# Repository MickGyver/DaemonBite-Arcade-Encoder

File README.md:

# DaemonBite-Arcade-Encoder
This is an arcade controller project for the MiSTer FPGA project and any other device accepting USB HID joysticks using an Arduino Pro Micro. This project can also be used to create a NeoGeo/Atari/Commodore/Amiga controller to USB adapters.

This project is an open source "lite" version of an arcade encoder I sell in my shop. If you want to support my work I sell the fully featured ones at https://daemonbite.com.

The input lag for an arcade controller or adapter built around this project is minimal. Here is the result from a test with a 1ms polling rate on a MiSTer with this project:

| Samples | Average | Max | Min | Std Dev |
| ------ | ------ | ------ | ------ | ------ | 
| 13962 | 0.74ms | 1.28ms | 0.23ms | 0.29ms |

## Wiring (Arcade Controller)
The wiring is simple. Connect one leg of each microswitch to GND and the other leg to the digital pin according to the schematic below. That's it!  

## Recommended layout (for PS3 stick compatibility)
Blue text in image (silk screen) corresponds to the Bx button numbers in the image for wiring above. 

## Wiring (NeoGeo USB Adapter)

## Wiring (Atari/Commodore/Amiga USB Adapter)

## Programming the Arduino
1. Download the free Arduino IDE: https://www.arduino.cc/en/main/software
2. Connect the Arduino Pro Micro to a USB port and let the drivers install.
3. Choose the correct board and virtual COM port in the IDE.
3. Compile/Upload the project.

## License
This project is licensed under the GNU General Public License v3.0. The name "daemonbite" is registered to my company in Finland and should not be used by others.

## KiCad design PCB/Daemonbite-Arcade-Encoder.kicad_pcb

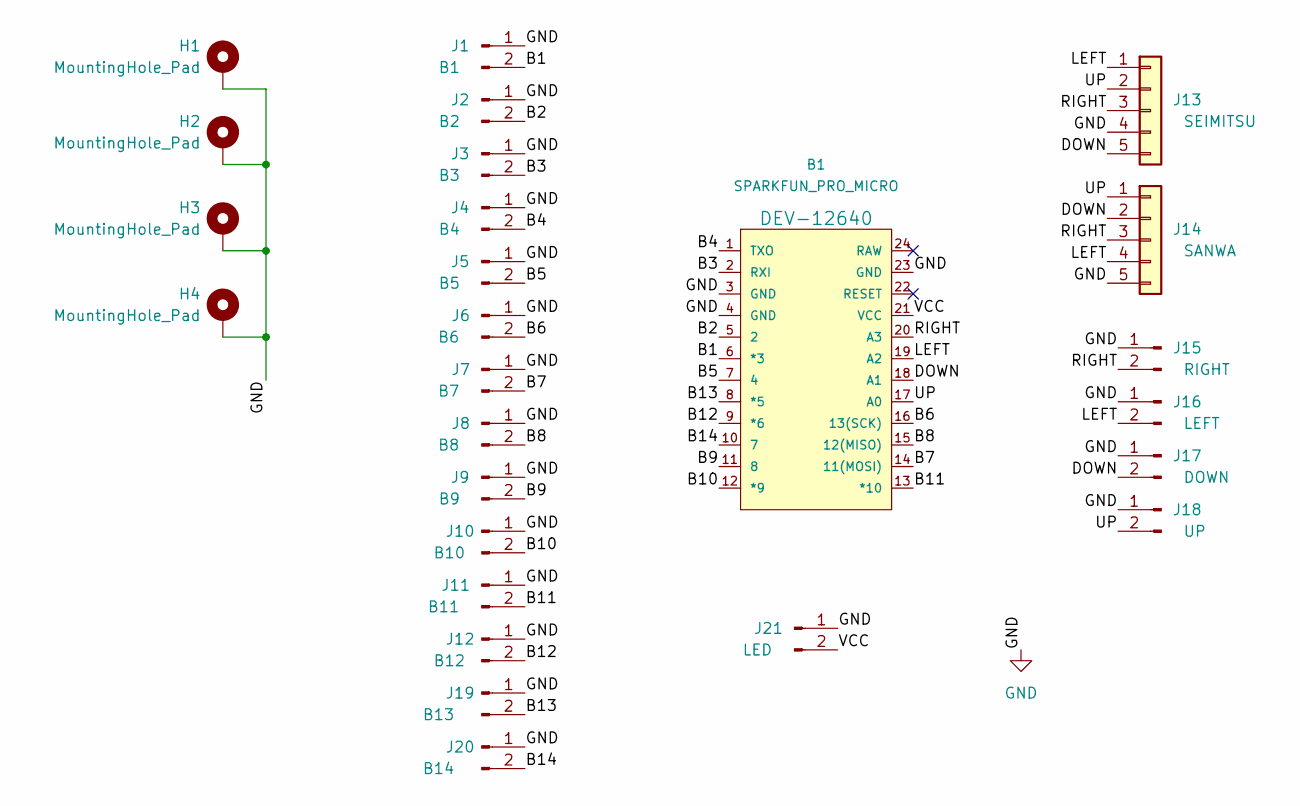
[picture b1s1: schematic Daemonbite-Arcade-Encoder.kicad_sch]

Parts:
B1: SPARKFUN_PRO_MICRO; ProMicro-NoSilk
H1, H2, H3, H4: MountingHole_Pad; MountingHole_3.2mm_M3_Pad
J1: B1; JST_XH_B2B-XH-A_1x02_P2.50mm_Vertical
J2: B2; JST_XH_B2B-XH-A_1x02_P2.50mm_Vertical
J3: B3; JST_XH_B2B-XH-A_1x02_P2.50mm_Vertical
J4: B4; JST_XH_B2B-XH-A_1x02_P2.50mm_Vertical
J5: B5; JST_XH_B2B-XH-A_1x02_P2.50mm_Vertical
J6: B6; JST_XH_B2B-XH-A_1x02_P2.50mm_Vertical
J7: B7; JST_XH_B2B-XH-A_1x02_P2.50mm_Vertical
J8: B8; JST_XH_B2B-XH-A_1x02_P2.50mm_Vertical
J9: B9; JST_XH_B2B-XH-A_1x02_P2.50mm_Vertical
J10: B10; JST_XH_B2B-XH-A_1x02_P2.50mm_Vertical
J11: B11; JST_XH_B2B-XH-A_1x02_P2.50mm_Vertical
J12: B12; JST_XH_B2B-XH-A_1x02_P2.50mm_Vertical
J13: SEIMITSU; JST_XH_B5B-XH-AM_1x05_P2.50mm_Vertical
J14: SANWA; JST_XH_B5B-XH-AM_1x05_P2.50mm_Vertical
J15: RIGHT; JST_XH_B2B-XH-A_1x02_P2.50mm_Vertical
J16: LEFT; JST_XH_B2B-XH-A_1x02_P2.50mm_Vertical
J17: DOWN; JST_XH_B2B-XH-A_1x02_P2.50mm_Vertical
J18: UP; JST_XH_B2B-XH-A_1x02_P2.50mm_Vertical
J19: B13; JST_XH_B2B-XH-A_1x02_P2.50mm_Vertical
J20: B14; JST_XH_B2B-XH-A_1x02_P2.50mm_Vertical
J21: LED; JST_XH_B2B-XH-A_1x02_P2.50mm_Vertical

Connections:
/B1: B1.6 (*3), J1.2
/B2: B1.5 (2), J2.2
/B3: B1.2 (RXI), J3.2
/B4: B1.1 (TXO), J4.2
/B5: B1.7 (4), J5.2
/B6: B1.16 (13(SCK)), J6.2
/B7: B1.14 (11(MOSI)), J7.2
/B8: B1.15 (12(MISO)), J8.2
/B9: B1.11 (8), J9.2
/B10: B1.12 (*9), J10.2
/B11: B1.13 (*10), J11.2
/B12: B1.9 (*6), J12.2
/B13: B1.8 (*5), J19.2
/B14: B1.10 (7), J20.2
/DOWN: B1.18 (A1), J13.5, J14.2, J17.2
/LEFT: B1.19 (A2), J13.1, J14.4, J16.2
/RIGHT: B1.20 (A3), J13.3, J14.3, J15.2
/UP: B1.17 (A0), J13.2, J14.1, J18.2
/VCC: B1.21 (VCC), J21.2
GND: B1.3 (GND), B1.4 (GND), B1.23 (GND), H1.1, H2.1, H3.1, H4.1, J1.1, J2.1, J3.1, J4.1, J5.1, J6.1, J7.1, J8.1, J9.1, J10.1, J11.1, J12.1, J13.4, J14.5, J15.1, J16.1, J17.1, J18.1, J19.1, J20.1, J21.1

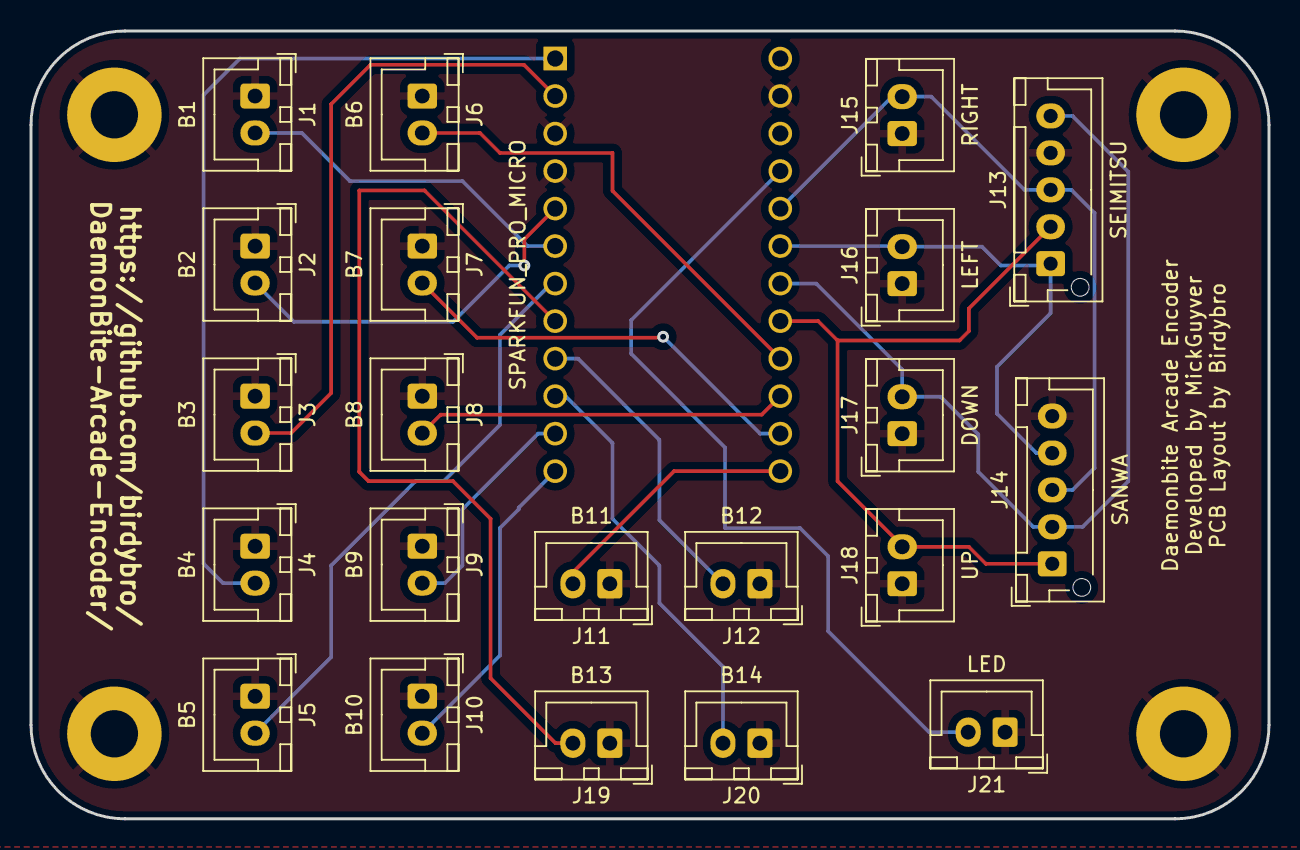
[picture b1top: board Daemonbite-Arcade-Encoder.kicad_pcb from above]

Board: 2 copper layers, 83.8 x 53.3 mm, 26 parts (0 on the bottom side), 20 nets.

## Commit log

2019-10-20 Initial version
2019-10-21 Support for up to 12 buttons
2019-10-21 Removed hex files
2020-01-20 Renamed the project
2020-01-20 Renamed images
2020-01-20 Updated the license text
2020-01-28 Debounce logic added.
2020-01-28 Fixed bug with buttons 9-12
2020-01-28 Uint8 bug fixed
2020-02-16 Changed START pin mapping for NeoGeo
2020-02-16 Debouncing disabled by default
2020-02-17 Debounce activated using #define
2020-03-13 Fixed a for-loop bug.
2020-05-11 Fixed a small bug
2020-05-14 Built in SOCD Cleaner
2020-05-31 Serial for USB endpoint added.
2020-07-08 PS3 stick compatibility added
2020-07-08 Layout image added
2020-07-08 Layout image updated.
2020-07-08 Wiring image updated
2020-08-28 Sanitize current millis in case of overflow.
2020-08-28 Fixing copy and paste error
2021-03-28 Fixing SOCD Cleaning on ps3 mode
2022-03-06 upload finished pcb and gerbers
2022-03-06 add stepfile and previews
2022-03-21 forgot one component
